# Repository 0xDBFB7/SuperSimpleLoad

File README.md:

# SuperSimpleLoad
An Arduino-compatible 150w electronic load, designed to be as simple as possible.

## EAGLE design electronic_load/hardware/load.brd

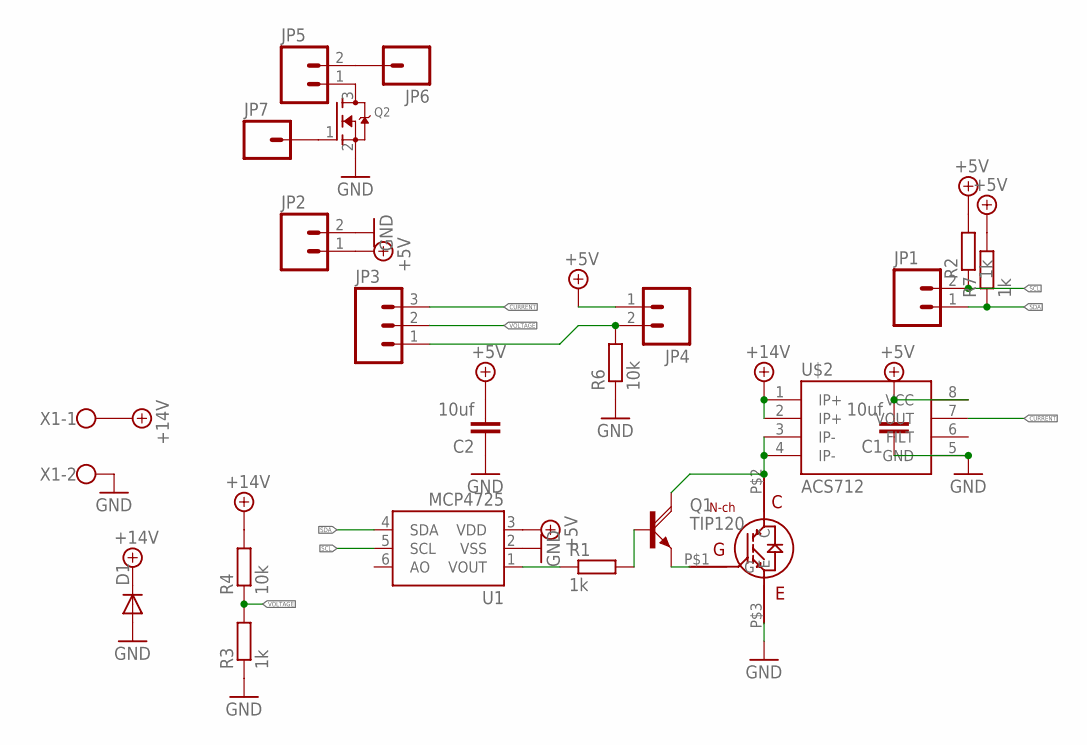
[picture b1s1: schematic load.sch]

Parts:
C1, C2: 10uf; C0603
D1: DIODE-TO220V; TO220ACS
JP1, JP2, JP4, JP5: M02PTH; 1X02
JP3: M03PTH; 1X03
JP6, JP7: M01PTH; 1X01
Q1: TIP120; TO220AH
Q2: MOSFET-NREFLOW; SOT23
R1, R2, R3, R7: 1k; R0603
R4, R6: 10k; R0603
U1: MCP4725; SOT23-6
U$1: TO-247A; TO-247
U$2: ACS712; SO08
X1: W237-102

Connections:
+5V: C1.2, C2.2, JP2.1, JP4.1, R2.2, R7.2, U1.3 (VDD), U$2.8 (VCC)
+14V: D1.C, R4.2, U$2.1 (IP+), U$2.2 (IP+), X1.1
CURRENT: JP3.3, U$2.7 (VOUT)
GND: C1.1, C2.1, D1.A, JP2.2, Q2.2 (S), R3.1, R6.1, U1.2 (VSS), U$1.P$3 (E), U$2.5 (GND), X1.2
unnamed: Q1.E, U$1.P$1 (G)
unnamed: JP7.1, Q2.1 (G)
unnamed: JP5.1, Q2.3 (D)
unnamed: JP5.2, JP6.1
unnamed: R1.1, U1.1 (VOUT)
unnamed: Q1.B, R1.2
unnamed: Q1.C, U$1.P$2 (C), U$2.3 (IP-), U$2.4 (IP-)
SCL: JP1.2, R2.1, U1.5 (SCL)
SDA: JP1.1, R7.1, U1.4 (SDA)
THERM: JP3.1, JP4.2, R6.2
VOLTAGE: JP3.2, R3.2, R4.1

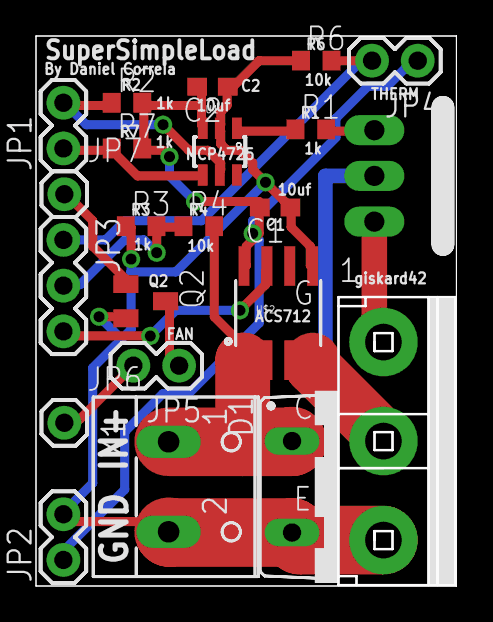
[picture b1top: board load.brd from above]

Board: 2 copper layers, 23.2 x 30.4 mm, 22 parts (0 on the bottom side), 15 nets.

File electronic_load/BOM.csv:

"40","1","277-6405-ND","1935776","CONN TERM BLOCK 2POS 5.0MM","LOAD","0","0.66000","$0.66"
"41","1","MJH6284GOS-ND","MJH6284G","TRANS NPN DARL 100V 20A TO247","LOAD","0","6.60000","$6.60"
"42","1","TIP120-ND","TIP120","TRANS NPN DARL 60V 5A TO-220","LOAD","0","0.94000","$0.94"
"43","1","620-1371-1-ND","ACS711ELCTR-25AB-T","SENSOR CURRENT HALL 25A AC/DC","LOAD","0","5.01000","$5.01"
"44","1","317-1258-ND","MF52A2103J3470","NTC THERMISTOR 10K OHM 5% BEAD","LOAD","0","0.63000","$0.63"
"47","1","MCP4725A0T-E/CHCT-ND","MCP4725A0T-E/CH","IC DAC 12BIT W/I2C SOT23A-6","LOAD","0","1.55000","$1.55"

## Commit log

2018-04-22 Added BOM

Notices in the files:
parts and their libraries:
SparkFun-Connectors: Licensing: Creative Commons ShareAlike 4.0 International - https://creativecommons.org/licenses/by-sa/4.0
